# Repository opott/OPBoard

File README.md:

# OPBoard
This is the first mechanical keyboard I have designed.

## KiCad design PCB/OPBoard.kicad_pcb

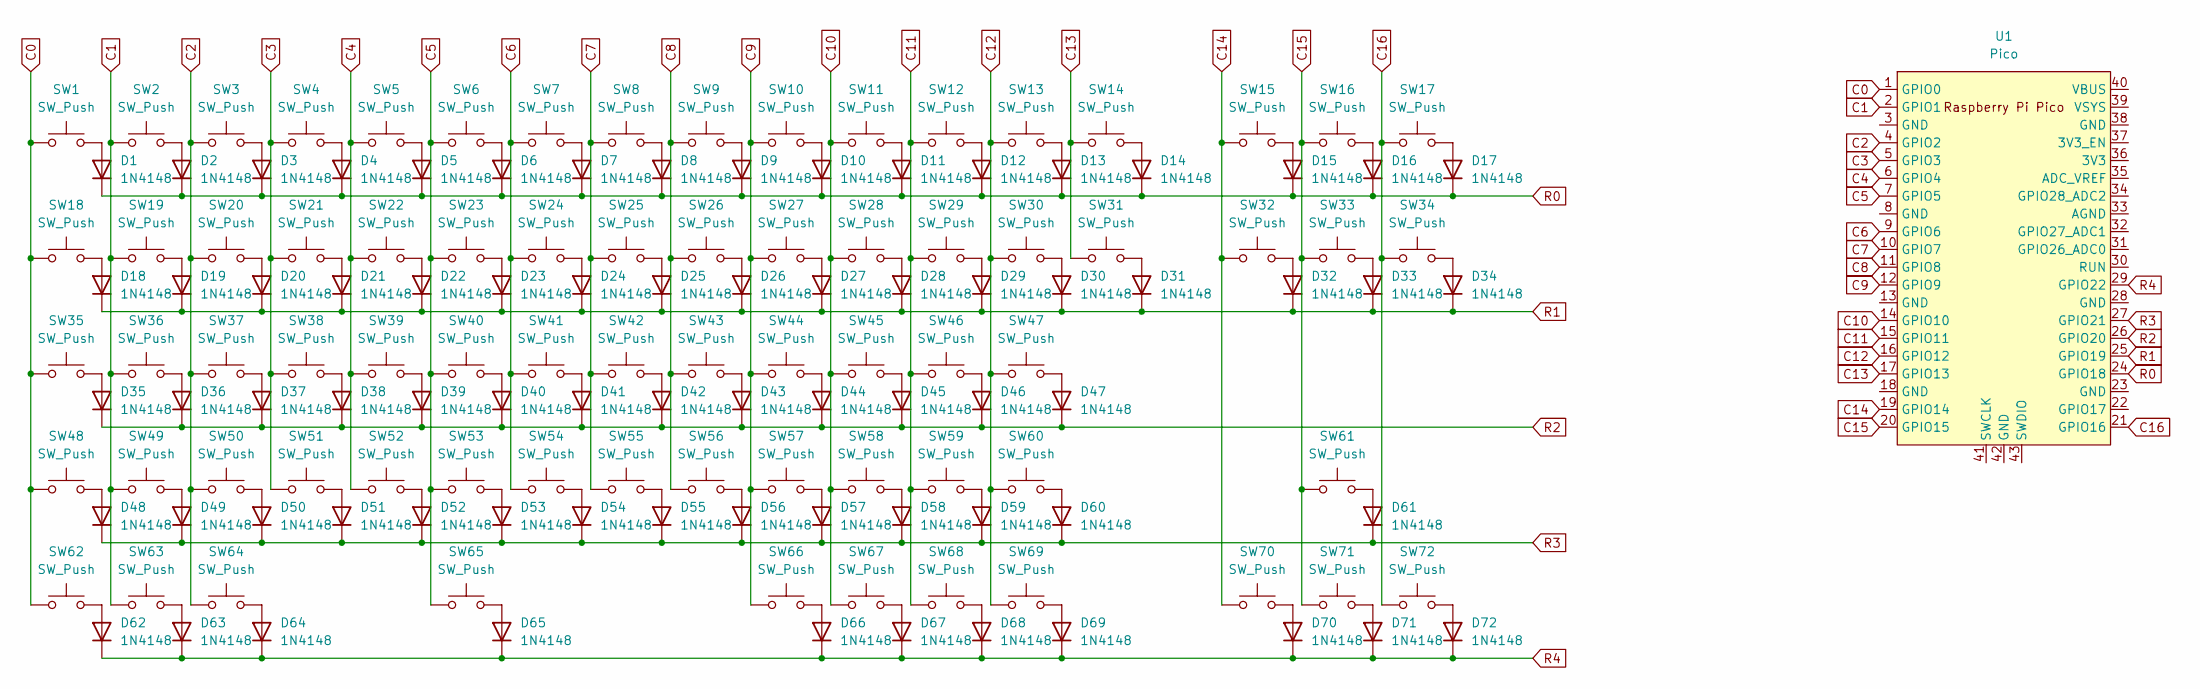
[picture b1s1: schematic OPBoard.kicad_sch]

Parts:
D1, D2, D3, D4, D5, D6, D7, D8, D9, D10, D11, D12, D13, D14, D15, D16, D17, D18, D19, D20, D21, D22, D23, D24, D25, D26, D27, D28, D29, D30, D31, D32, D33, D34, D35, D36, D37, D38, D39, D40, D41, D42, D43, D44, D45, D46, D47, D48, D49, D50, D51, D52, D53, D54, D55, D56, D57, D58, D59, D60, D61, D62, D63, D64, D65, D66, D67, D68, D69, D70, D71, D72: 1N4148; D_DO-35_SOD27_P7.62mm_Horizontal
SW1, SW2, SW3, SW4, SW5, SW6, SW7, SW8, SW9, SW10, SW11, SW12, SW13, SW15, SW16, SW17, SW19, SW20, SW21, SW22, SW23, SW24, SW25, SW26, SW27, SW28, SW29, SW30, SW32, SW33, SW34, SW36, SW37, SW38, SW39, SW40, SW41, SW42, SW43, SW44, SW45, SW46, SW47, SW49, SW50, SW51, SW52, SW53, SW54, SW55, SW56, SW57, SW58, SW59, SW61, SW70, SW71, SW72: SW_Push; MX-Alps-Hybrid-1U
SW14: SW_Push; MX-Alps-Hybrid-2U
SW18: SW_Push; MX-Alps-Hybrid-1.5U
SW31: SW_Push; MX-Alps-Hybrid-ISO
SW35: SW_Push; MX-Alps-Hybrid-1.75U
SW48, SW62, SW63, SW64, SW66, SW67, SW68, SW69: SW_Push; MX-Alps-Hybrid-1.25U
SW60: SW_Push; MX-Alps-Hybrid-2.75U
SW65: SW_Push; MX-Alps-Hybrid-6.25U
U1: Pico; RPi_Pico_SMD_TH

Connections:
C0: SW1.1, SW18.1, SW35.1, SW48.1, SW62.1, U1.1 (GPIO0)
C1: SW2.1, SW19.1, SW36.1, SW49.1, SW63.1, U1.2 (GPIO1)
C2: SW3.1, SW20.1, SW37.1, SW50.1, SW64.1, U1.4 (GPIO2)
C3: SW4.1, SW21.1, SW38.1, SW51.1, U1.5 (GPIO3)
C4: SW5.1, SW22.1, SW39.1, SW52.1, U1.6 (GPIO4)
C5: SW6.1, SW23.1, SW40.1, SW53.1, SW65.1, U1.7 (GPIO5)
C6: SW7.1, SW24.1, SW41.1, SW54.1, U1.9 (GPIO6)
C7: SW8.1, SW25.1, SW42.1, SW55.1, U1.10 (GPIO7)
C8: SW9.1, SW26.1, SW43.1, SW56.1, U1.11 (GPIO8)
C9: SW10.1, SW27.1, SW44.1, SW57.1, SW66.1, U1.12 (GPIO9)
C10: SW11.1, SW28.1, SW45.1, SW58.1, SW67.1, U1.14 (GPIO10)
C11: SW12.1, SW29.1, SW46.1, SW59.1, SW68.1, U1.15 (GPIO11)
C12: SW13.1, SW30.1, SW47.1, SW60.1, SW69.1, U1.16 (GPIO12)
C13: SW14.1, SW31.1, U1.17 (GPIO13)
C14: SW15.1, SW32.1, SW70.1, U1.19 (GPIO14)
C15: SW16.1, SW33.1, SW61.1, SW71.1, U1.20 (GPIO15)
C16: SW17.1, SW34.1, SW72.1, U1.21 (GPIO16)
unnamed: D1.2 (A), SW1.2
unnamed: D2.2 (A), SW2.2
unnamed: D3.2 (A), SW3.2
unnamed: D4.2 (A), SW4.2
unnamed: D5.2 (A), SW5.2
unnamed: D6.2 (A), SW6.2
unnamed: D7.2 (A), SW7.2
unnamed: D8.2 (A), SW8.2
unnamed: D9.2 (A), SW9.2
unnamed: D10.2 (A), SW10.2
unnamed: D11.2 (A), SW11.2
unnamed: D12.2 (A), SW12.2
unnamed: D13.2 (A), SW13.2
unnamed: D14.2 (A), SW14.2
unnamed: D15.2 (A), SW15.2
unnamed: D16.2 (A), SW16.2
unnamed: D17.2 (A), SW17.2
unnamed: D18.2 (A), SW18.2
unnamed: D19.2 (A), SW19.2
unnamed: D20.2 (A), SW20.2
unnamed: D21.2 (A), SW21.2
unnamed: D22.2 (A), SW22.2
unnamed: D23.2 (A), SW23.2
unnamed: D24.2 (A), SW24.2
unnamed: D25.2 (A), SW25.2
unnamed: D26.2 (A), SW26.2
unnamed: D27.2 (A), SW27.2
unnamed: D28.2 (A), SW28.2
unnamed: D29.2 (A), SW29.2
unnamed: D30.2 (A), SW30.2
unnamed: D31.2 (A), SW31.2
unnamed: D32.2 (A), SW32.2
unnamed: D33.2 (A), SW33.2
unnamed: D34.2 (A), SW34.2
unnamed: D35.2 (A), SW35.2
unnamed: D36.2 (A), SW36.2
unnamed: D37.2 (A), SW37.2
unnamed: D38.2 (A), SW38.2
unnamed: D39.2 (A), SW39.2
unnamed: D40.2 (A), SW40.2
unnamed: D41.2 (A), SW41.2
unnamed: D42.2 (A), SW42.2
unnamed: D43.2 (A), SW43.2
unnamed: D44.2 (A), SW44.2
unnamed: D45.2 (A), SW45.2
unnamed: D46.2 (A), SW46.2
unnamed: D47.2 (A), SW47.2
unnamed: D48.2 (A), SW48.2
unnamed: D49.2 (A), SW49.2
unnamed: D50.2 (A), SW50.2
unnamed: D51.2 (A), SW51.2
unnamed: D52.2 (A), SW52.2
unnamed: D53.2 (A), SW53.2
unnamed: D54.2 (A), SW54.2
unnamed: D55.2 (A), SW55.2
unnamed: D56.2 (A), SW56.2
unnamed: D57.2 (A), SW57.2
unnamed: D58.2 (A), SW58.2
unnamed: D59.2 (A), SW59.2
unnamed: D60.2 (A), SW60.2
unnamed: D61.2 (A), SW61.2
unnamed: D62.2 (A), SW62.2
unnamed: D63.2 (A), SW63.2
unnamed: D64.2 (A), SW64.2
unnamed: D65.2 (A), SW65.2
unnamed: D66.2 (A), SW66.2
unnamed: D67.2 (A), SW67.2
unnamed: D68.2 (A), SW68.2
unnamed: D69.2 (A), SW69.2
unnamed: D70.2 (A), SW70.2
unnamed: D71.2 (A), SW71.2
unnamed: D72.2 (A), SW72.2
R0: D1.1 (K), D2.1 (K), D3.1 (K), D4.1 (K), D5.1 (K), D6.1 (K), D7.1 (K), D8.1 (K), D9.1 (K), D10.1 (K), D11.1 (K), D12.1 (K), D13.1 (K), D14.1 (K), D15.1 (K), D16.1 (K), D17.1 (K), U1.24 (GPIO18)
R1: D18.1 (K), D19.1 (K), D20.1 (K), D21.1 (K), D22.1 (K), D23.1 (K), D24.1 (K), D25.1 (K), D26.1 (K), D27.1 (K), D28.1 (K), D29.1 (K), D30.1 (K), D31.1 (K), D32.1 (K), D33.1 (K), D34.1 (K), U1.25 (GPIO19)
R2: D35.1 (K), D36.1 (K), D37.1 (K), D38.1 (K), D39.1 (K), D40.1 (K), D41.1 (K), D42.1 (K), D43.1 (K), D44.1 (K), D45.1 (K), D46.1 (K), D47.1 (K), U1.26 (GPIO20)
R3: D48.1 (K), D49.1 (K), D50.1 (K), D51.1 (K), D52.1 (K), D53.1 (K), D54.1 (K), D55.1 (K), D56.1 (K), D57.1 (K), D58.1 (K), D59.1 (K), D60.1 (K), D61.1 (K), U1.27 (GPIO21)
R4: D62.1 (K), D63.1 (K), D64.1 (K), D65.1 (K), D66.1 (K), D67.1 (K), D68.1 (K), D69.1 (K), D70.1 (K), D71.1 (K), D72.1 (K), U1.29 (GPIO22)

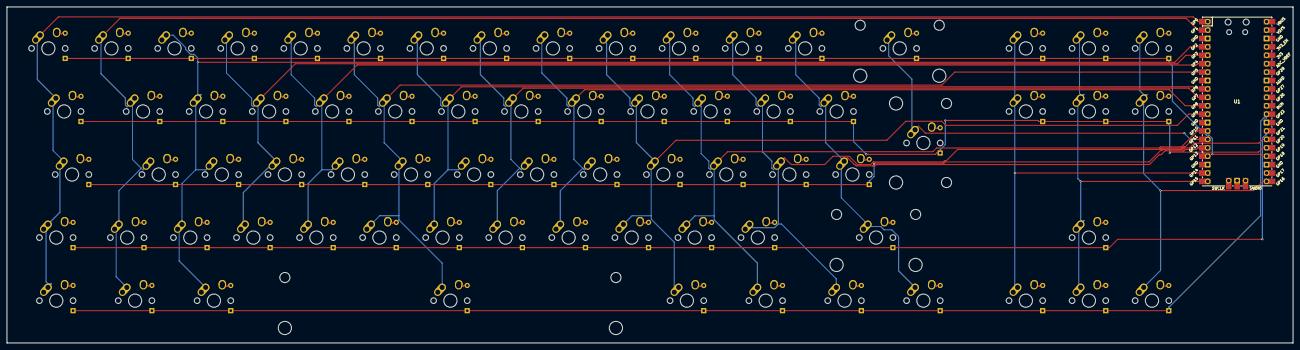
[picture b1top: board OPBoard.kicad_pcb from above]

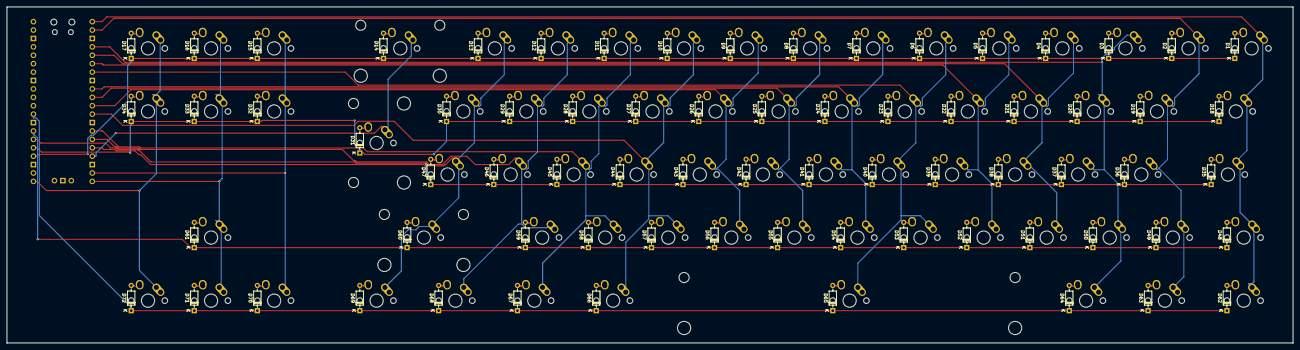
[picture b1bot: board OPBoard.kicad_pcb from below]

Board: 2 copper layers, 388.5 x 101.5 mm, 145 parts (72 on the bottom side), 94 nets.

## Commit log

2025-01-28 [ImgBot] Optimize images
    /image.png -- 168.54kb -> 137.25kb (18.56%)
